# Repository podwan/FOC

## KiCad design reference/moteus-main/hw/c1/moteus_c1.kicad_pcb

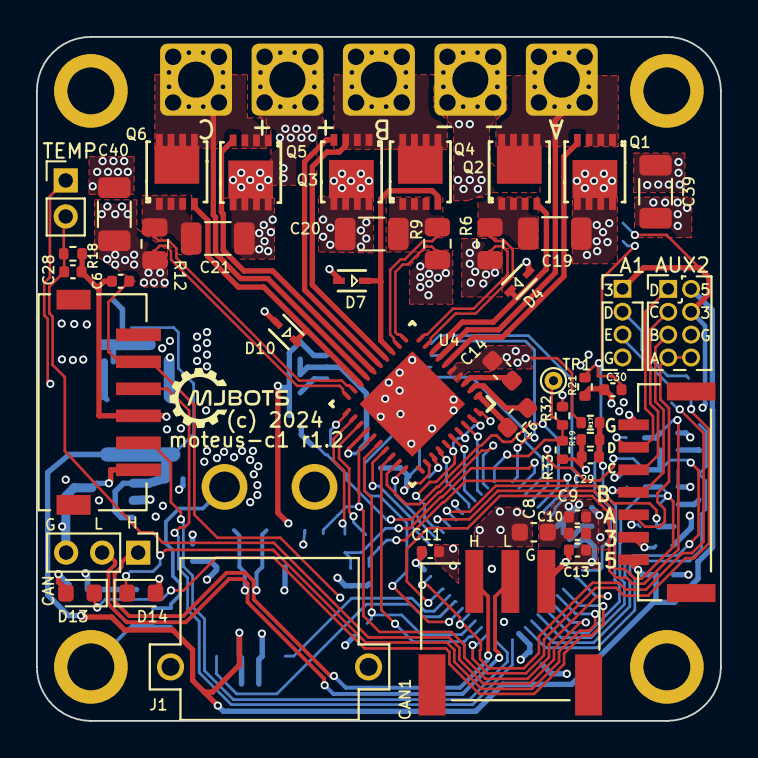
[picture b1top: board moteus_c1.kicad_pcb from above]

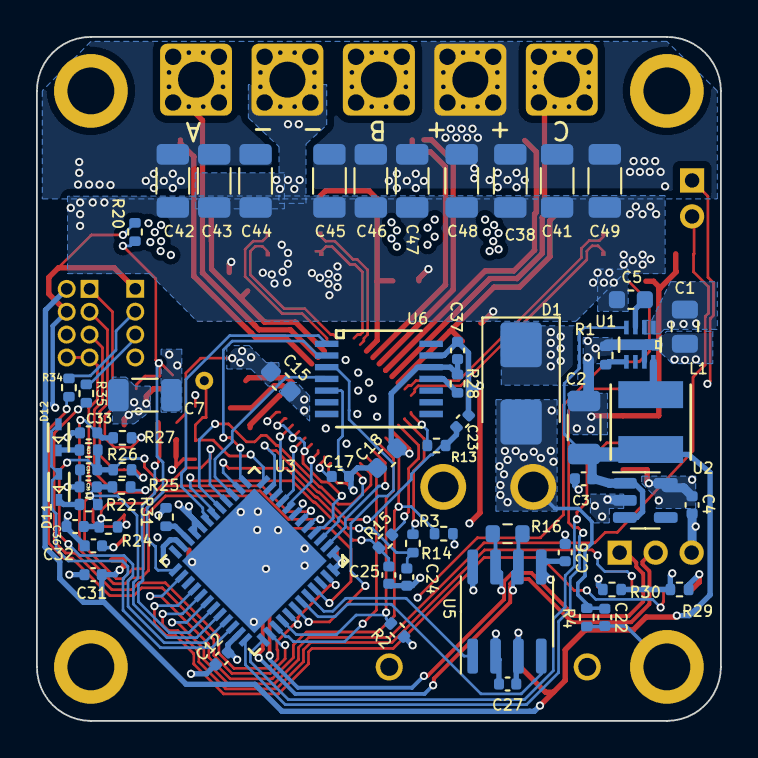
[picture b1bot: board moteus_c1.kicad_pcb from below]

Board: 4 copper layers, 38.0 x 38.0 mm, 125 parts (64 on the bottom side), 83 nets.

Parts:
AUX1: Conn_01x04; PinHeader_1x04_P1.27mm_Vertical
AUX2: SM07B-GHS-TB(LF)(SN); JST_SM07B-GHS-TB(LF)(SN)
AUX2H1: Conn_02x04_Odd_Even; PinHeader_2x04_P1.27mm_Vertical
C1: 1uF 100V; C_0805_2012Metric
C2: 22uF; C_1206_3216Metric
C3, C4, C10, C17, C31, C32: 1uF; C_0402_1005Metric
C5, C18: 1uF; C_0603_1608Metric
C6, C9, C11, C12, C13, C26, C27, C28, C29, C30, C37: 0.1uF; C_0402_1005Metric
C7: 10uF; C_1206_3216Metric
C8: 4.7uF; C_0603_1608Metric
C14: 1uF 25V; C_0603_1608Metric
C15: 0.1uF 100V; C_0603_1608Metric
C16: 47nF 100V; C_0603_1608Metric
C19, C20, C21: 0.1uF 100V; C_1206_3216Metric
C22, C33, C34, C35, C36: DNP; C_0402_1005Metric
C23, C24, C25: 1000pF; C_0402_1005Metric
C38, C39, C40, C41, C42, C43, C44, C45, C46, C47, C48, C49: 4.7uF 100V; C_1206_3216Metric
CAN1: S3B-PH-SM4-TB(LF)(SN); JST_S3B-PH-SM4-TB(LF)(SN)
CAN_DBG1: Conn_01x03_Pin; PinHeader_1x03_P2.00mm_Vertical
D1: SMBJ48D-M3/I; D_SMB
D4, D7, D10, D11, D12: BAT41KFILM; SOD-523_STM
D13, D14: LED; LED_0603_1608Metric
J1: XT30PW-M; AMASS_XT30PW-M
L1: 47uH; IND_4018-WE-LQS_WRE
MOUNT1, MOUNT2, MOUNT3, MOUNT4: M2.5_MOUNT
NT1: NetTie_2; NetTie-2_SMD_Pad0.254mm
NT2, NT3, NT4, NT5, NT6, NT7: NetTie_2; NetTie-2_SMD_Pad0.2
Q1, Q2, Q3, Q4, Q5, Q6: TPN19008QM_LQ; TSON Advance_TOS
R1, R28: 0; R_0402_1005Metric
R2, R3, R22, R23, R31: 2k; R_0402_1005Metric
R4, R32: DNP; R_0402_1005Metric
R6, R9, R12: 2mOhm; R_0805_2012Metric
R13, R14, R15: 22; R_0402_1005Metric
R16: 120; R_0603_1608Metric
R17: 100k 1%; R_0402_1005Metric
R18, R21: 10k 1%; R_0402_1005Metric
R19: 4.7k 1%; R_0402_1005Metric
R20: 47k NTC; R_0402_1005Metric
R24, R25, R26, R27, R34, R35: 100; R_0402_1005Metric
R29, R30: 560; R_0402_1005Metric
R33: 100k; R_0402_1005Metric
SWD1: S6B-ZR-SM4A-TF(LF)(SN); JST_S6B-ZR-SM4A-TF(LF)(SN)
TEMP1: Conn_01x02_Pin; PinHeader_1x02_P2.00mm_Vertical
TP1: TestPoint; TestPoint_THTPad_D1.0mm_Drill0.5mm
U1: MAX15062BATA+T; 21-0487A_MXM
U2: TLV70233PDBVR; SOT-23-5
U3: STM32G474CEU6; UFQFPN-48_7X7X0P55MM
U4: DRV8323SRTAR; RTA0040B
U5: TCAN1057AEV-Q1; SOIC-8_3.9x4.9mm_P1.27mm
U6: AS5047P-ATSM; TSSOP14_OSM
VN1: Conn_01x01; POWER_M2.5
VP1: Conn_01x01; POWER_M2.5
X1, X2, X3: Conn_01x01; POWER_M2.5

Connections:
+3V: AUX1.1, AUX2.2, AUX2H1.4, C4.1, C7.1, C8.1, C9.1, C10.1, C11.1, C12.1, C13.1, C18.2, C26.1, C32.1, C37.1, R2.1, R3.1, R20.1, R28.2, R29.1, R30.1, R32.1, SWD1.6, TEMP1.1, U2.5 (OUT), U3.1 (VBAT), U3.20 (VREF+), U3.21 (VDDA), U3.23 (VDD), U3.35 (VDD), U3.48 (VDD), U4.24 (VREF), U5.5 (VIO), U6.12 (VDD3V)
+5V: AUX2.1, AUX2H1.2, C2.1, C3.1, C27.1, C31.1, L1.1, U1.4 (FB/VOUT), U2.1 (IN), U2.3 (EN), U5.3 (VCC)
/CAN/CAN_N: CAN1.2, CAN_DBG1.2, R16.2, U5.6 (CANL)
/CAN/CAN_P: CAN1.1, CAN_DBG1.1, R16.1, U5.7 (CANH)
/CAN/CAN_RX: U3.43 (PB5), U5.4 (RXD)
/CAN/CAN_TX: U3.44 (PB6), U5.1 (TXD)
/Current Sense/CUR1: R13.1, U4.21 (SOC)
/Current Sense/CUR2: R14.1, U4.22 (SOB)
/Current Sense/CUR3: R15.1, U4.23 (SOA)
/Current Sense/FCUR1: C23.1, R13.2, U3.11 (PA3)
/Current Sense/FCUR2: C24.1, R14.2, U3.14 (PA6)
/Current Sense/FCUR3: C25.1, R15.2, U3.18 (PB1)
/Gate Driver/DRV8323_CS: U3.17 (PB0), U4.29 (GAIN_SCS_N)
/Gate Driver/DRV8323_FAULT: R3.2, U3.26 (PB13), U4.25 (FAULT_N)
/Gate Driver/DRV8323_MISO: R2.2, U3.40 (PC11), U4.26 (MODE_SDO)
/Gate Driver/DRV8323_MOSI: U3.2 (PC13), U4.27 (IDRIVE_SDI)
/Gate Driver/DRV8323_SCLK: U3.39 (PC10), U4.28 (VDS_SCLK)
/Gate Driver/GHA: Q1.4 (GATE), U4.6 (GHA)
/Gate Driver/GHB: Q3.4 (GATE), U4.15 (GHB)
/Gate Driver/GHC: Q5.4 (GATE), U4.16 (GHC)
/Gate Driver/GLA: D4.1, Q2.4 (GATE), U4.8 (GLA)
/Gate Driver/GLB: D7.1, Q4.4 (GATE), U4.13 (GLB)
/Gate Driver/GLC: D10.1, Q6.4 (GATE), U4.18 (GLC)
/Gate Driver/MOTOR1: U3.8 (PA0), U4.34 (INHA)
/Gate Driver/MOTOR2: U3.9 (PA1), U4.36 (INHB)
/Gate Driver/MOTOR3: U3.10 (PA2), U4.38 (INHC)
/Gate Driver/MOTOR_ENABLE: U3.3 (PC14-OSC32_IN), U4.30 (ENABLE)
/Gate Driver/MOTOR_HIZ: U3.4 (PC15-OSC32_OUT), U4.35 (INLA), U4.37 (INLB), U4.39 (INLC)
/H Bridge A/OUTX: Q1.1 (SOURCE), Q1.2 (SOURCE), Q1.3 (SOURCE), Q2.5 (DRAIN), Q2.6 (DRAIN), Q2.7 (DRAIN), Q2.8 (DRAIN), U4.7 (SHA), X1.1
/H Bridge A/SPX_Q: C19.2, NT2.2, Q2.1 (SOURCE), Q2.2 (SOURCE), Q2.3 (SOURCE), R6.1
/H Bridge A/SXX_N: NT3.1, U4.10 (SNA)
/H Bridge A/SXX_P: NT2.1, U4.9 (SPA)
/H Bridge B/OUTX: Q3.1 (SOURCE), Q3.2 (SOURCE), Q3.3 (SOURCE), Q4.5 (DRAIN), Q4.6 (DRAIN), Q4.7 (DRAIN), Q4.8 (DRAIN), U4.14 (SHB), X2.1
/H Bridge B/SPX_Q: C20.2, NT4.2, Q4.1 (SOURCE), Q4.2 (SOURCE), Q4.3 (SOURCE), R9.1
/H Bridge B/SXX_N: NT5.1, U4.11 (SNB)
/H Bridge B/SXX_P: NT4.1, U4.12 (SPB)
/H Bridge C/OUTX: Q5.1 (SOURCE), Q5.2 (SOURCE), Q5.3 (SOURCE), Q6.5 (DRAIN), Q6.6 (DRAIN), Q6.7 (DRAIN), Q6.8 (DRAIN), U4.17 (SHC), X3.1
/H Bridge C/SPX_Q: C21.2, NT6.2, Q6.1 (SOURCE), Q6.2 (SOURCE), Q6.3 (SOURCE), R12.1
/H Bridge C/SXX_N: NT7.1, U4.20 (SNC)
/H Bridge C/SXX_P: NT6.1, U4.19 (SPC)
/LED Sense/DAC: R32.2, R33.1, TP1.1, U3.12 (PA4)
/LED Sense/LED1: D13.1 (K), U3.28 (PB15)
/LED Sense/LED2: D14.1 (K), U3.29 (PC6)
/VT Sense/VBAT_SENSE: C29.1, R17.2, R19.1, U3.31 (PA9)
/VT Sense/VTEMP_FET: C30.1, R20.2, R21.1, U3.25 (PB12)
/VT Sense/VTEMP_MOT: C28.1, R18.1, TEMP1.2, U3.30 (PA8)
/aux1/AS5047_CS: U3.19 (PB2), U6.1 (CSn)
/aux1/AUX1P_D: AUX1.2, R34.1
/aux1/AUX1P_E: AUX1.3, R35.1
/aux1/AUX1_A: U3.13 (PA5), U6.2 (CLK)
/aux1/AUX1_B: U3.42 (PB4), U6.3 (MISO)
/aux1/AUX1_C: U3.15 (PA7), U6.4 (MOSI)
/aux1/AUX1_D: R34.2, U3.38 (PA15)
/aux1/AUX1_E: R35.2, U3.41 (PB3), U3.47 (PB9)
/aux2/AUX2P_A: AUX2.3, AUX2H1.7, AUX2H1.8, R24.1
/aux2/AUX2P_B: AUX2.4, AUX2H1.5, R25.1
/aux2/AUX2P_C: AUX2.5, AUX2H1.3, R26.1
/aux2/AUX2P_D: AUX2.6, AUX2H1.1, R27.1
/aux2/AUX2_A: C36.1, R24.2, U3.6 (PF1-OSC_OUT)
/aux2/AUX2_B: C35.1, R22.2, R25.2, U3.5 (PF0-OSC_IN), U3.32 (PA10)
/aux2/AUX2_C: C34.1, R23.2, R26.2, U3.16 (PC4), U3.33 (PA11)
/aux2/AUX2_D: C33.1, R27.2, U3.45 (PB7)
/aux2/AUX2_I2C_PULLUP: D11.2, D12.2, U3.34 (PA12)
/stm32g4/NRST: C6.1, SWD1.2, U3.7 (PG10-NRST)
/stm32g4/SWCLK: SWD1.5, U3.37 (PA14)
/stm32g4/SWDIO: SWD1.3, U3.36 (PA13)
GND: AUX1.4, AUX2.7, AUX2H1.6, C2.2, C3.2, C4.2, C6.2, C7.2, C8.2, C9.2, C10.2, C11.2, C12.2, C13.2, C17.1, C18.1, C23.2, C24.2, C25.2, C26.2, C27.2, C28.2, C29.2, C30.2, C31.2, C32.2, C33.2, C34.2, C35.2, C36.2, C37.2, CAN1.3, CAN_DBG1.3, NT1.2, R1.2, R18.2, R19.2, R21.2, R31.2, R33.2, SWD1.4, U1.7 (GND), U2.2 (GND), U3.49 (EPAD), U4.32 (AGND), U5.2 (GND), U5.8 (STB), U6.5 (TEST), U6.13 (GND)
GNDPWR: C1.2, C5.2, C15.1, C22.2, C38.2, C39.2, C40.2, C41.2, C42.2, C43.2, C44.2, C45.2, C46.2, C47.2, C48.2, C49.2, D1.2 (A2), D4.2, D7.2, D10.2, J1.N, NT1.1, NT3.2, NT5.2, NT7.2, R4.2, R6.2, R9.2, R12.2, U4.40 (PGND), U4.41 (PAD), VN1.1
MOUNT_GND: C22.1, MOUNT3.1, R4.1
unnamed: D11.1, R22.1
unnamed: D12.1, R23.1
unnamed: D13.2 (A), R29.2
unnamed: D14.2 (A), R30.2
unnamed: L1.2, U1.8 (LX)
unnamed: R1.1, U1.5 (MODE)
unnamed: C5.1, U1.3 (VCC)
unnamed: R31.1, U3.22 (PB10)
unnamed: C16.2, U4.2 (CPH)
unnamed: C16.1, U4.1 (CPL)
unnamed: C17.2, U4.33 (DVDD)
unnamed: C14.2, U4.3 (VCP)
unnamed: R28.1, U6.11 (VDD)
V+: C1.1, C14.1, C15.2, C19.1, C20.1, C21.1, C38.1, C39.1, C40.1, C41.1, C42.1, C43.1, C44.1, C45.1, C46.1, C47.1, C48.1, C49.1, D1.1 (A1), J1.P, Q1.5 (DRAIN), Q1.6 (DRAIN), Q1.7 (DRAIN), Q1.8 (DRAIN), Q3.5 (DRAIN), Q3.6 (DRAIN), Q3.7 (DRAIN), Q3.8 (DRAIN), Q5.5 (DRAIN), Q5.6 (DRAIN), Q5.7 (DRAIN), Q5.8 (DRAIN), R17.1, U1.1 (VIN), U1.2 (EN/UVLO), U4.4 (VM), U4.5 (VDRAIN), VP1.1

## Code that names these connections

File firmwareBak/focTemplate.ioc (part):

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Mcu.Name=STM32G431C(6-8-B)Ux
Mcu.Package=UFQFPN48
Mcu.UserName=STM32G431CBUx
PA0.Mode=IN1-Single-Ended
PA0.Signal=ADC2_IN1
PA1.Mode=Standalone
PA1.Signal=OPAMP1_VINP
PA10.Signal=S_TIM1_CH3
PA11.Mode=FDCAN_Activate
PA11.Signal=FDCAN1_RX
PA12.Mode=FDCAN_Activate
PA12.Signal=FDCAN1_TX
PA13.Mode=Serial_Wire
PA13.Signal=SYS_JTMS-SWDIO
PA14.Mode=Serial_Wire
PA14.Signal=SYS_JTCK-SWCLK
PA15.Signal=GPIO_Output
PA2.Signal=SharedAnalog_PA2
PA3.Mode=Standalone
PA3.Signal=OPAMP1_VINM
PA4.GPIOParameters=GPIO_Speed,PinState,GPIO_Label
PA4.GPIO_Label=SPI1_CS
PA4.GPIO_Speed=GPIO_SPEED_FREQ_VERY_HIGH
PA4.PinState=GPIO_PIN_SET
PA4.Signal=GPIO_Output
PA5.Mode=Standalone
PA5.Signal=OPAMP2_VINM
PA6.Signal=SharedAnalog_PA6
PA7.Mode=Standalone
PA7.Signal=OPAMP2_VINP
PA8.Signal=S_TIM1_CH1
PA9.Signal=S_TIM1_CH2
PB0.Mode=Standalone
PB0.Signal=OPAMP3_VINP
PB1.Signal=SharedAnalog_PB1
PB10.Mode=Asynchronous
PB10.Signal=USART3_TX
PB11.Mode=Asynchronous
PB11.Signal=USART3_RX
PB12.Mode=IN11-Single-Ended
PB12.Signal=ADC1_IN11
PB13.Mode=PWM Generation1 CH1 CH1N
PB13.Signal=TIM1_CH1N
PB14.Mode=PWM Generation2 CH2 CH2N
PB14.Signal=TIM1_CH2N
PB15.Mode=PWM Generation3 CH3 CH3N
PB15.Signal=TIM1_CH3N
PB2.Mode=Standalone
PB2.Signal=OPAMP3_VINM
PB3.Mode=Full_Duplex_Master
PB3.Signal=SPI1_SCK
PB4.Mode=Full_Duplex_Master
PB4.Signal=SPI1_MISO
PB5.Mode=Full_Duplex_Master
PB5.Signal=SPI1_MOSI
PB6.Signal=S_TIM4_CH1
PB7.Signal=S_TIM4_CH2
PB8-BOOT0.Signal=S_TIM4_CH3
PB9.Signal=GPIO_Output
PC10.Signal=GPIO_Input
PC11.Signal=GPIO_Input
PC13.Signal=GPIO_Input
PC4.GPIOParameters=GPIO_Label
PC4.GPIO_Label=LED2
PC4.Signal=GPIO_Output
PC6.GPIOParameters=GPIO_Label
PC6.GPIO_Label=LED1
PC6.Signal=GPIO_Output
PF0-OSC_IN.Mode=HSE-External-Oscillator
PF0-OSC_IN.Signal=RCC_OSC_IN
PF1-OSC_OUT.Mode=HSE-External-Oscillator
PF1-OSC_OUT.Signal=RCC_OSC_OUT
RCC.HSE_VALUE=24000000
RCC.SYSCLKFreq_VALUE=160000000
RCC.SYSCLKSource=RCC_SYSCLKSOURCE_PLLCLK
board=custom

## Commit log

2024-03-26 ready to add foc algrithem
2024-05-06 串口发送与电流环有冲突？
2024-05-07 完成电流闭环
2024-05-07 velocityLooping
2024-05-07 完善串口中
2024-05-08 角度环调参中
2024-05-09 梳理流程中
2024-05-09 完善电流环中
2024-05-11 准备实现电压速度闭环
2024-05-13 continuing angle voltage loop
2024-05-14 电流环闭环中
2024-05-15 closed current torque loop
2024-05-15 closed current loops
2024-05-15 to knob
2024-05-16 udpate
2024-05-24 add mpu6050
2024-06-02 update pcn
2024-06-13 update hall
2024-07-27 go senseless
2024-08-01 update firmware
2024-08-04 speedlooping

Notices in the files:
reference/moteus-main/hw/c1/moteus_c1.kicad_pcb:
(c) 2024
